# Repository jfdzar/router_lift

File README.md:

# router_lift
Documentation of the automatic router lift for the ultimate workbench - Munich Maker Lab

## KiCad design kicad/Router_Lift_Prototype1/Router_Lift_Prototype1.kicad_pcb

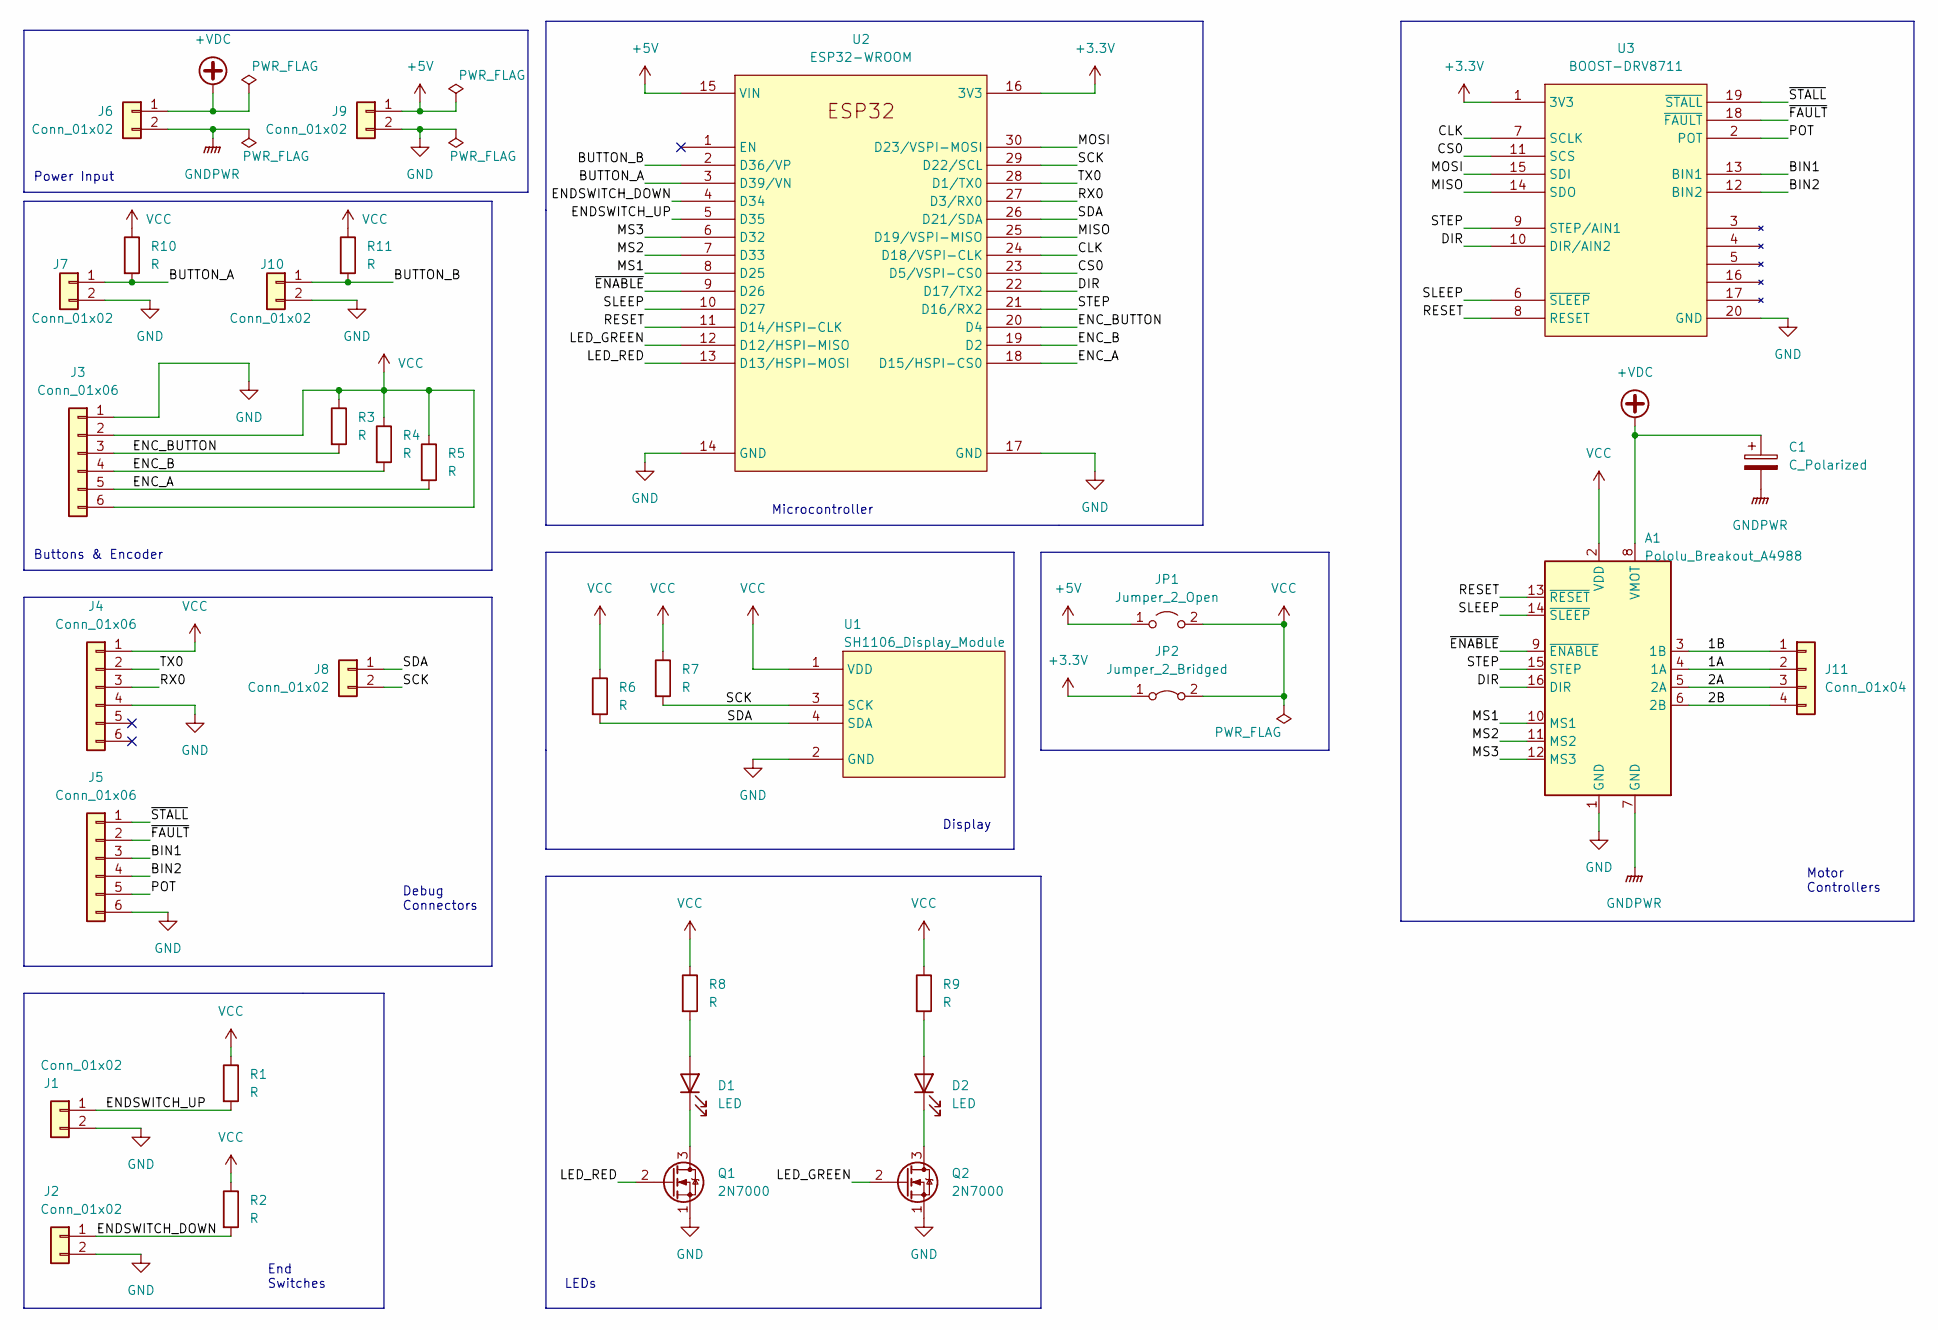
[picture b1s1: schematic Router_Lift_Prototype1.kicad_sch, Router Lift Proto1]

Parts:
A1: Pololu_Breakout_A4988; Pololu_Breakout-16_15.2x20.3mm
C1: C_Polarized; CP_Radial_D6.3mm_P2.50mm
D1, D2: LED; LED_D3.0mm
J1, J2, J6, J7, J8, J9, J10: Conn_01x02; TerminalBlock_TE_282834-2_1x02_P2.54mm_Horizontal
J3, J4, J5: Conn_01x06; TerminalBlock_TE_282834-6_1x06_P2.54mm_Horizontal
J11: Conn_01x04; TerminalBlock_TE_282834-4_1x04_P2.54mm_Horizontal
JP1: Jumper_2_Open; PinHeader_1x02_P2.54mm_Vertical
JP2: Jumper_2_Bridged; PinHeader_1x02_P2.54mm_Vertical
Q1, Q2: 2N7000; TO-92_Inline
R1, R2, R3, R4, R5, R6, R7, R8, R9, R10, R11: R; R_Axial_DIN0207_L6.3mm_D2.5mm_P10.16mm_Horizontal
U1: SH1106_Display_Module; SH1106_Makershop
U2: ESP32-WROOM
U3: BOOST-DRV8711; TI_BOOST_DRV8711

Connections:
+3V3: JP2.1 (A), U2.16 (3V3), U3.1 (3V3)
+5V: J9.1, JP1.1 (A), U2.15 (VIN)
+VDC: A1.8 (VMOT), C1.1, J6.1
/1A: A1.4 (1A), J11.2
/1B: A1.3 (1B), J11.1
/2A: A1.5 (2A), J11.3
/2B: A1.6 (2B), J11.4
/BIN1: J5.3, U3.13 (BIN1)
/BIN2: J5.4, U3.12 (BIN2)
/BUTTON_A: J7.1, R10.2, U2.3 (D39/VN)
/BUTTON_B: J10.1, R11.2, U2.2 (D36/VP)
/CLK: U2.24 (D18/VSPI-CLK), U3.7 (SCLK)
/CS0: U2.23 (D5/VSPI-CS0), U3.11 (SCS)
/DIR: A1.16 (DIR), U2.22 (D17/TX2), U3.10 (DIR/AIN2)
/ENC_A: J3.5, R5.2, U2.18 (D15/HSPI-CS0)
/ENC_B: J3.4, R4.2, U2.19 (D2)
/ENC_BUTTON: J3.3, R3.2, U2.20 (D4)
/ENDSWITCH_DOWN: J2.1, R2.2, U2.4 (D34)
/ENDSWITCH_UP: J1.1, R1.2, U2.5 (D35)
/LED_GREEN: Q2.2 (G), U2.12 (D12/HSPI-MISO)
/LED_RED: Q1.2 (G), U2.13 (D13/HSPI-MOSI)
/MISO: U2.25 (D19/VSPI-MISO), U3.14 (SDO)
/MOSI: U2.30 (D23/VSPI-MOSI), U3.15 (SDI)
/MS1: A1.10 (MS1), U2.8 (D25)
/MS2: A1.11 (MS2), U2.7 (D33)
/MS3: A1.12 (MS3), U2.6 (D32)
/POT: J5.5, U3.2 (POT)
/RESET: A1.13 (~RESET), U2.11 (D14/HSPI-CLK), U3.8 (RESET)
/RX0: J4.3, U2.27 (D3/RX0)
/SCK: J8.2, R7.2, U1.3 (SCK), U2.29 (D22/SCL)
/SDA: J8.1, R6.2, U1.4 (SDA), U2.26 (D21/SDA)
/SLEEP: A1.14 (~SLEEP), U2.10 (D27), U3.6 (~SLEEP)
/STEP: A1.15 (STEP), U2.21 (D16/RX2), U3.9 (STEP/AIN1)
/TX0: J4.2, U2.28 (D1/TX0)
/~ENABLE: A1.9 (~ENABLE), U2.9 (D26)
/~FAULT: J5.2, U3.18 (~FAULT)
/~STALL: J5.1, U3.19 (~STALL)
GND: A1.1 (GND), J1.2, J2.2, J3.1, J4.4, J5.6, J7.2, J9.2, J10.2, Q1.1 (S), Q2.1 (S), U1.2 (GND), U2.14 (GND), U2.17 (GND), U3.20 (GND)
GNDPWR: A1.7 (GND), C1.2, J6.2
unnamed: D1.1 (K), Q1.3 (D)
unnamed: D1.2 (A), R8.2
unnamed: D2.1 (K), Q2.3 (D)
unnamed: D2.2 (A), R9.2
VCC: A1.2 (VDD), J3.2, J3.6, J4.1, JP1.2 (B), JP2.2 (B), R1.1, R2.1, R3.1, R4.1, R5.1, R6.1, R7.1, R8.1, R9.1, R10.1, R11.1, U1.1 (VDD)

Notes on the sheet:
Debug Connectors
Buttons & Encoder
Power Input
Microcontroller
LEDs
Display
End Switches
Motor Controllers

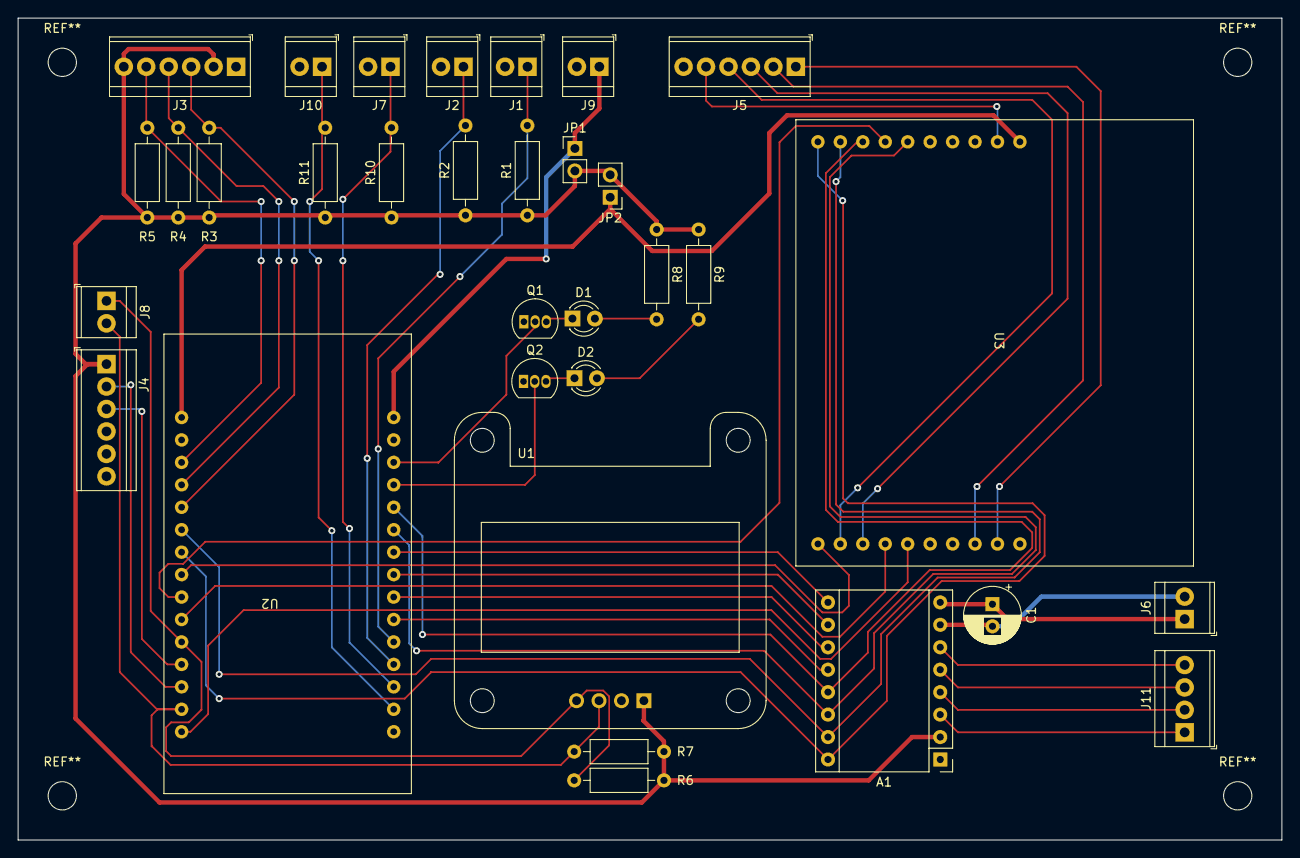
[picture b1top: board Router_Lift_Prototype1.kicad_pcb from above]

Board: 2 copper layers, 143.0 x 93.0 mm, 33 parts (0 on the bottom side), 44 nets.

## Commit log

2022-02-13 Original Commit Code Router Lift
2022-02-13 Original Commit of code - Working movement and controling display
2022-02-22 Tests with encoder and Datasheets upload
2022-03-08 Added bluetooth functionality
2022-03-15 Basic Functionality working - bluetooth removed
2022-03-29 Solved speed issue - display.display was delaying the loop
2022-04-02 Working Prototype with different Speeds
2022-04-02 Refactored Code with Motor and Display classes
2022-04-02 Motor Stopping when reaching endstop and position updating
2022-04-03 functionality working - still bug on stop possition from endstops
2022-04-03 First documentation of the code
2022-04-03 Add picture of the pinout
2022-04-03 show image
2022-04-03 Added chapters
2022-04-09 Original Commit of Prototype PCB
2022-04-09 Added Datasheets to the doc
2022-04-09 Linked further footprints and first placing
2022-04-10 Component placement and start routing test
2022-04-10 Further placement
2022-04-19 Completing Layout - Several Pin changes to be updated in Software
2022-04-20 Finished routing before curving tracks and review
2022-04-24 updated gitignore to avoid kicad files
2022-04-24 add project and jobs files
2022-04-24 Changes in code to add SPI Controller Interface
2022-04-24 Updated changes in the PCB to include SPI changes
2022-04-25 Added changes working with BOOST-DRV8711 Controller
2022-05-17 Created the board with DRV8711 Integration
2022-05-17 Added modes to interface to modify speed for testing
2022-05-17 Modify files with speed change functionality
2022-06-23 Added monitor port to platformio.ini
2022-06-23 Updated position limit
2022-06-23 Added change current feature
2022-06-23 Added draw modes
2022-06-23 Added speed limit and modes functionality
2022-06-23 removed end stops from RouterLiftMotor
2022-07-09 Commiting to avoid losing information
2022-07-18 add functionality endswithces
2022-07-30 test commit
